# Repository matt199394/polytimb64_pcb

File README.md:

Polytimb64 is a polyfonic midi interface to connect commodore 64 to  midi keyboard by means the user port. I found this project by chance on youtube https://www.youtube.com/watch?v=LIM-qxfz80c 
The author have made a full and comprensive guide to to build the hardware and how to use the c64 software https://notevoto.4lima.de/PolyTimb64_Main_EN.html
In this repository I would share a custom PCB that in addiction to the original hardware implement a little oled display and a a midi thru connector

I'm not a musician but the softwre is very powerfull with many setting like pulse width, filter and pich modulation

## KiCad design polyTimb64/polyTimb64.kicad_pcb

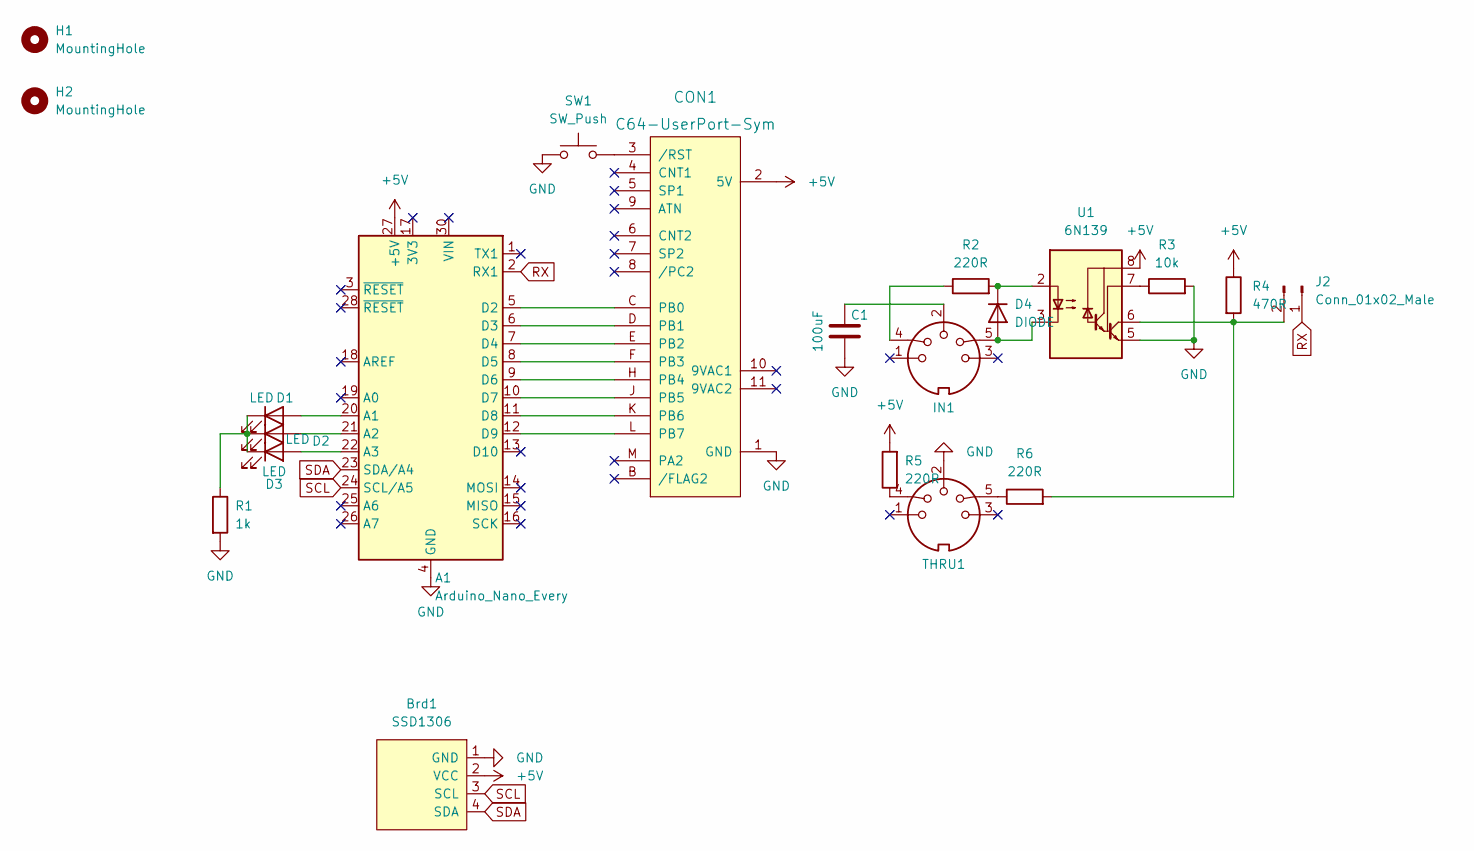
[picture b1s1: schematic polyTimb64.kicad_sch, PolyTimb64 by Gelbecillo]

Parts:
A1: Arduino_Nano_Every; Arduino_Nano
Brd1: SSD1306; 128x64OLED_I2C
C1: 100uF; C_Disc_D5.1mm_W3.2mm_P5.00mm
CON1: C64-UserPort-Sym; C64-User-Port-Female_Single-GND
D1, D2, D3: LED; LED_D3.0mm
D4: DIODE; D_DO-35_SOD27_P7.62mm_Horizontal
H1, H2: MountingHole; MountingHole_3.2mm_M3_DIN965_Pad_TopBottom
IN1: DIN-5_180degree; DIN-5-midi
J2: Conn_01x02_Male; PinHeader_1x02_P2.54mm_Vertical
R1: 1k; R_Axial_DIN0207_L6.3mm_D2.5mm_P7.62mm_Horizontal
R2, R5, R6: 220R; R_Axial_DIN0207_L6.3mm_D2.5mm_P7.62mm_Horizontal
R3: 10k; R_Axial_DIN0207_L6.3mm_D2.5mm_P7.62mm_Horizontal
R4: 470R; R_Axial_DIN0207_L6.3mm_D2.5mm_P7.62mm_Horizontal
SW1: SW_Push; SW_Tactile_SPST_Angled_PTS645Vx58-2LFS
THRU1: DIN-5_180degree; DIN-5-midi
U1: 6N139; DIP-8_W7.62mm

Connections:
+5V: A1.27 (+5V), Brd1.2 (VCC), CON1.2 (5V), R4.1, R5.2, U1.8 (VCC)
GND: A1.4 (GND), A1.29 (GND), Brd1.1 (GND), C1.2, CON1.1 (GND), R1.2, R3.2, SW1.1, THRU1.2, U1.5 (GND); also elsewhere on the board
unnamed: A1.5 (D2), CON1.C (PB0)
unnamed: A1.6 (D3), CON1.D (PB1)
unnamed: A1.7 (D4), CON1.E (PB2)
unnamed: A1.8 (D5), CON1.F (PB3)
unnamed: A1.9 (D6), CON1.H (PB4)
unnamed: A1.10 (D7), CON1.J (PB5)
unnamed: A1.11 (D8), CON1.K (PB6)
unnamed: A1.12 (D9), CON1.L (PB7)
unnamed: A1.20 (A1), D1.2 (A)
unnamed: A1.21 (A2), D2.2 (A)
unnamed: A1.22 (A3), D3.2 (A)
unnamed: C1.1, IN1.2
unnamed 14: CON1.3 (/RST), SW1.2; also elsewhere on the board
unnamed: D1.1 (K), D2.1 (K), D3.1 (K), R1.1
unnamed: D4.1 (A), IN1.5, U1.3 (C2)
unnamed: D4.2 (K), R2.2, U1.2 (C1)
unnamed: IN1.4, R2.1
unnamed: J2.2, R4.2, R6.2, U1.6 (VO2)
unnamed: R3.1, U1.7 (VO1)
unnamed: R5.1, THRU1.4
unnamed: R6.1, THRU1.5
RX: A1.2 (RX1), J2.1
SCL: A1.24 (SCL/A5), Brd1.3 (SCL)
SDA: A1.23 (SDA/A4), Brd1.4 (SDA)

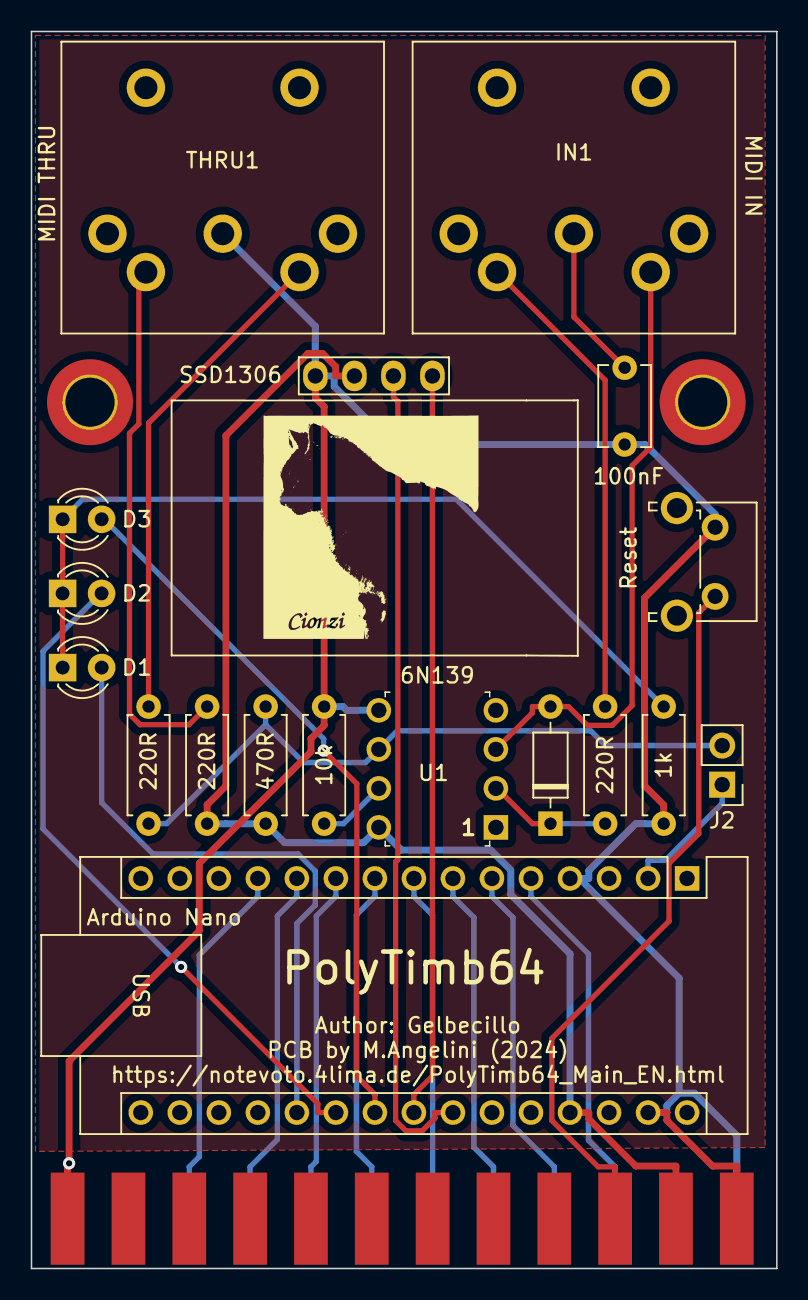
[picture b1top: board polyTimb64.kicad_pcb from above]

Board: 2 copper layers, 48.5 x 80.5 mm, 22 parts (0 on the bottom side), 26 nets.

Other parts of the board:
 : LOGO; cionzi
Reset: SW_Push; SW_Tactile_SPST_Angled_PTS645Vx58-2LFS

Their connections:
GND: Reset.1; also elsewhere on the board
unnamed 14: Reset.2; also elsewhere on the board
